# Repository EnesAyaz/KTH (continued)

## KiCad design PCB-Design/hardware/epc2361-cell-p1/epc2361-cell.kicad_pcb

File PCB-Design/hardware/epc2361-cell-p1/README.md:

# P1: EPC-style one-pair power-loop layout

This is the revised native KiCad 7 project requested from EPC's optimal-loop illustration. The original P0 project is preserved in the sibling directory. Open `epc2361-cell.kicad_pro` here.

## What changed

- 27 x 30 mm study outline. One high-side EPC2361 at (15,16) mm and one low-side at (15,22) mm; 6 mm pitch.
- Six 0805 capacitors across the top above the high-side device, with positive terminals facing the devices. Broad top DC+ copper replaces the long side rail.
- Capacitor negative terminals connect through paired vias to the first inner DC- layer. Low-side source vias complete the return directly beneath the top power path.
- Six optional/DNP bottom capacitors sit underneath the top bank. Their rail transitions are outside the device lands. The DC+ via antipads perforate L2 locally but leave a continuous return; their effect needs extraction. Bottom parts are not assumed equally effective at high frequencies.
- No driver IC. Individual top G/Kelvin-source contact pairs, series gate-resistor sites and optional local gate-source resistors remain.
- All power ports and seven probe pads are routed. Pads are interface placeholders, not selected or rated power sockets. Probe mapping: TP1 GH, TP2 high-side source/AC, TP3 GL, TP4 low-side source/DC-, TP5 DC+, TP6 DC-, TP7 AC.
- Insulated top cold-plate contact corridor reserved over the FET pair. Full plate, TIM, mounting and clamping remain mechanical design work.

## Capacitors

C1-C6: TDK C2012X7S2A105K125AB, 1 uF / 100 V / X7S / 0805, six populated provisionally. C7-C12 use the same part but are DNP until impedance and heating justify population. Nominal capacitance is 6 uF top-only or 12 uF with both banks; neither number is the retained capacitance at 75 V.

TDK's simple equivalent-circuit model gives 0.480 nH for this component. The six-capacitor ideal uncoupled component-only result is 0.080 nH. This excludes mounting, shared copper, vias, FET interconnections and coupling, and is not the complete loop inductance. The 1210 alternative has 0.600 nH model inductance and more nominal capacitance. These are conventional MLCCs selected for a low-inductance assembled bank; no suitable 100 V reverse-geometry part was verified.

See `../../docs/capacitor-selection-p1.md` for manufacturer links, alternatives and qualification limits. C at 75 V and capacitor RMS heating remain unqualified. External bulk capacitance is still required.

## Proposed stackup

The board file records a provisional four-layer stack: 70 um top copper, 100 um prepreg to the 35 um L2 return, 1.19 mm core, 35 um L3, 100 um prepreg, and 70 um bottom copper. Copper plus dielectric totals 1.60 mm before solder mask. FR4 electrical properties are placeholders, not a selected laminate. Fabricator confirmation is required. L3 currently has no functional plane; layer count alone does not reduce the loop.

The key optimization parameter is the 0.10 mm top-to-L2 separation. A parallel-plate estimate must use the actual overlapping current corridor and include transitions separately. No extracted or measured inductance is claimed.

## Checks and release status

30 components and 60 pin assignments match the KiCad-exported schematic netlist and PCB. Native PCB DRC: zero violations, zero unconnected pads, zero footprint errors. Native schematic ERC has not been run. Views: `top.svg`, `return.svg`, `bottom.svg`; PNG previews alongside them. Bottom export is viewed through the board from above unless mirrored in KiCad.

This is a routed engineering study, not a manufacturing release or a demonstrated 36.7 A RMS cell rating. Wide power distribution, terminal ratings, assembly footprint sign-off, capacitor derating, coupled parasitic extraction, switching tests and electrothermal validation are outstanding. The six-parallel module and gate-driver PCB are deferred.

## Rebuild

Run `scripts/build_cell_p1.py` with KiCad Python. Set `CELL_REVISION=epc2361-cell-p1`, run `scripts/build_cell_schematic.py`, export the XML netlist to this folder, then run `scripts/check_cell.py` with the same environment variable. The audit fills zones and writes the DRC report. Preserve manual edits before regenerating.

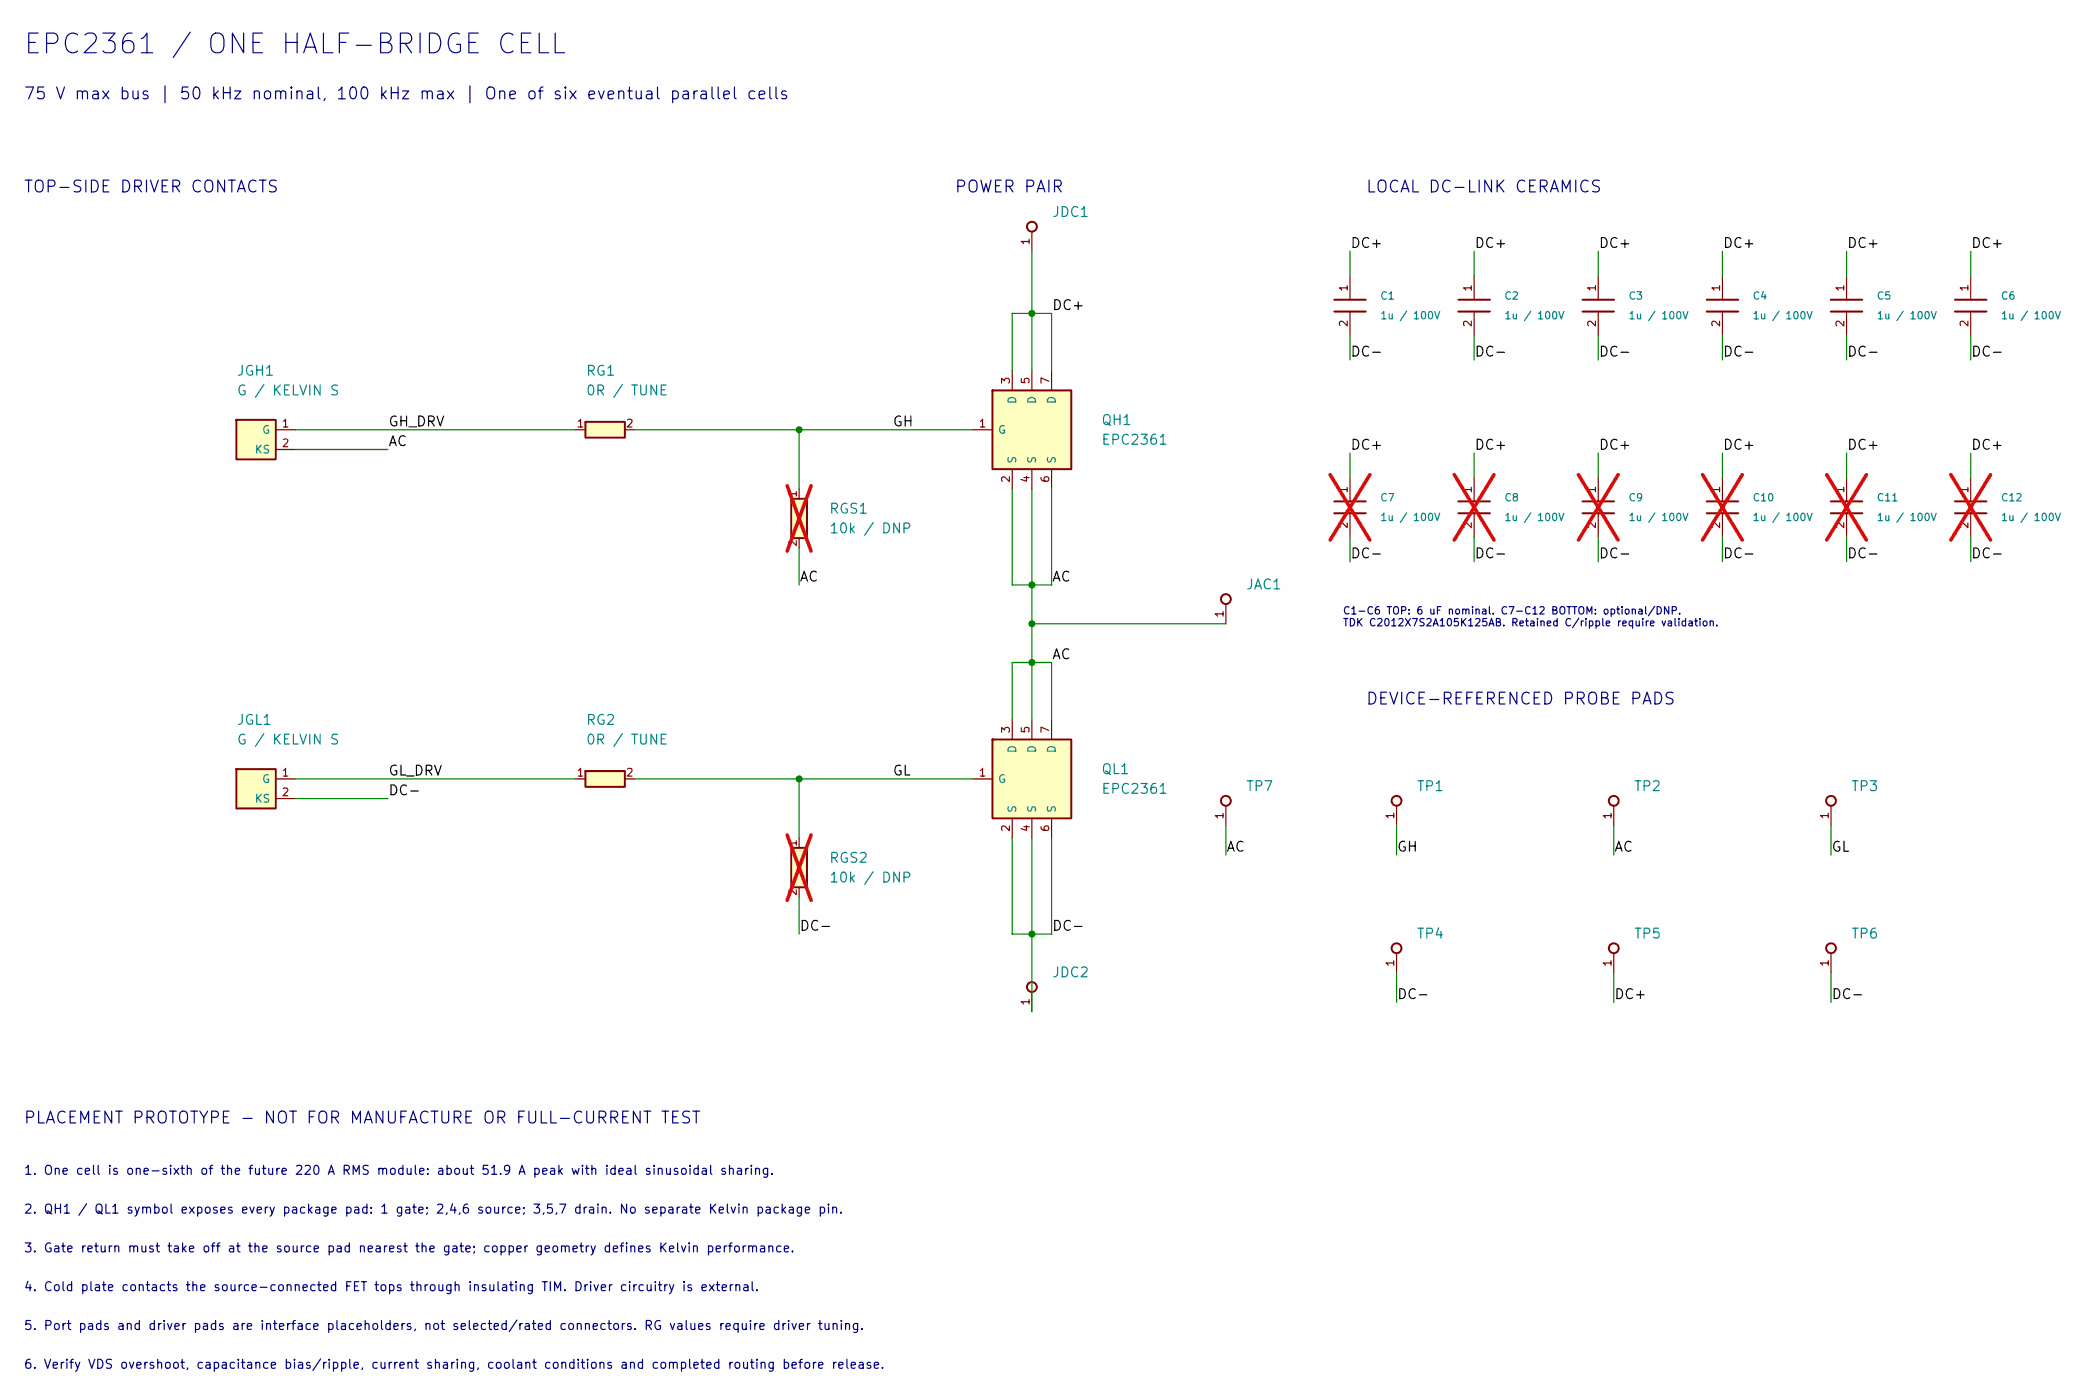
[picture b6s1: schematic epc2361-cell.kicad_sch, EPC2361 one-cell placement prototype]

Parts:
C1, C2, C3, C4, C5, C6: 1u / 100V; C_0805_2012Metric
C7, C8, C9, C10, C11, C12: 1u / 100V; C_0805_2012Metric; not fitted
JAC1: AC PORT PAD; Power_Port_Pad
JDC1: DC+ PORT PAD; Power_Port_Pad
JDC2: DC- PORT PAD; Power_Port_Pad
JGH1: G / KELVIN S; Gate_Source_Pads
JGL1: G / KELVIN S; Gate_Source_Pads
QH1: EPC2361
QL1: EPC2361
RG1, RG2: 0R / TUNE; R_0402_1005Metric
RGS1, RGS2: 10k / DNP; R_0402_1005Metric; not fitted
TP1: GH; Probe_Pad
TP2, TP7: AC; Probe_Pad
TP3: GL; Probe_Pad
TP4, TP6: DC-; Probe_Pad
TP5: DC+; Probe_Pad

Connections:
AC: JAC1.1, JGH1.2 (KS), QH1.2 (S), QH1.4 (S), QH1.6 (S), QL1.3 (D), QL1.5 (D), QL1.7 (D), RGS1.2, TP2.1, TP7.1
DC+: C1.1, C2.1, C3.1, C4.1, C5.1, C6.1, C7.1, C8.1, C9.1, C10.1, C11.1, C12.1, JDC1.1, QH1.3 (D), QH1.5 (D), QH1.7 (D), TP5.1
DC-: C1.2, C2.2, C3.2, C4.2, C5.2, C6.2, C7.2, C8.2, C9.2, C10.2, C11.2, C12.2, JDC2.1, JGL1.2 (KS), QL1.2 (S), QL1.4 (S), QL1.6 (S), RGS2.2, TP4.1, TP6.1
GH: QH1.1 (G), RG1.2, RGS1.1, TP1.1
GH_DRV: JGH1.1 (G), RG1.1
GL: QL1.1 (G), RG2.2, RGS2.1, TP3.1
GL_DRV: JGL1.1 (G), RG2.1

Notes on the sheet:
EPC2361 / ONE HALF-BRIDGE CELL
75 V max bus | 50 kHz nominal, 100 kHz max | One of six eventual parallel cells
TOP-SIDE DRIVER CONTACTS
POWER PAIR
LOCAL DC-LINK CERAMICS
C1-C6 TOP: 6 uF nominal. C7-C12 BOTTOM: optional/DNP. TDK C2012X7S2A105K125AB. Retained C/ripple require validation.
DEVICE-REFERENCED PROBE PADS
PLACEMENT PROTOTYPE - NOT FOR MANUFACTURE OR FULL-CURRENT TEST
1. One cell is one-sixth of the future 220 A RMS module: about 51.9 A peak with ideal sinusoidal sharing.
2. QH1 / QL1 symbol exposes every package pad: 1 gate; 2,4,6 source; 3,5,7 drain. No separate Kelvin package pin.
3. Gate return must take off at the source pad nearest the gate; copper geometry defines Kelvin performance.
4. Cold plate contacts the source-connected FET tops through insulating TIM. Driver circuitry is external.
5. Port pads and driver pads are interface placeholders, not selected/rated connectors. RG values require driver tuning.
6. Verify VDS overshoot, capacitance bias/ripple, current sharing, coolant conditions and completed routing before release.

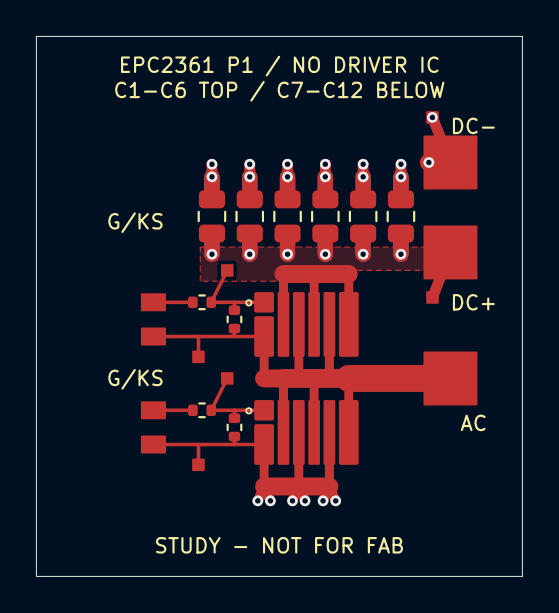
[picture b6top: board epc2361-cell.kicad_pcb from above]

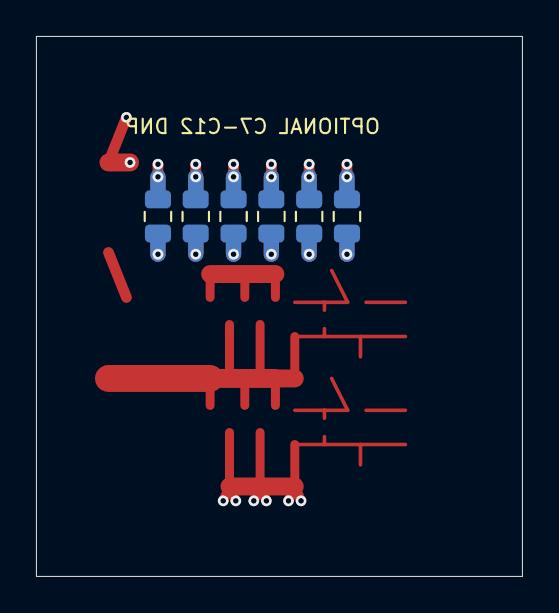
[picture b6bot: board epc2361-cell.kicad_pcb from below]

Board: 4 copper layers, 27.0 x 30.0 mm, 30 parts (6 on the bottom side), 7 nets.

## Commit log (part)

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2023-03-22 I will update this repo weekly with a report.
2023-04-24 I create a iterative loss analysis for only conduction losses
2023-04-24 switching loss is added
2023-04-25 established structs and generalized the script
2023-05-17 a new start
2023-05-30 weekly reports
    small literature review for bearing current is made
2023-05-31 updating the presentations
2023-06-02 weekly report about mitigation of bearing current
2023-06-05 Weekly reports are combined in Stepwise Design
2023-06-05 online carrier phase shift calculation to reduce the CMV
2023-06-05 for loop is created to calculate the phase requirements
2023-06-06 phases are calculated, it is a "paper" idea !!!
2023-06-06 updated version
2023-06-07 the presentation and analytic switching loop are updated
2023-06-07 presentation update
2023-06-08 create comparative analysis
2023-06-12 comparative analysis are added
2023-06-13 comparative analysis
2023-06-15 conduction losses and switching losses
2023-06-18 Hemizero presentation
2023-07-04 new common mode reduction method
    matlab model is created, a presentation is created
2023-07-04 loss calculations, for 2L and 3L converters
2023-07-18 dv/dt
2023-07-18 updated presentation
2023-08-29 weekly reports
2023-09-14 inmotion presentation
2023-09-14 inductance desing
2023-09-14 savings
2023-09-18 adding presentations
2023-10-04 gitignore
2023-11-16 loss calculation
2023-11-16 inductance
2023-11-16 modulation
2024-04-21 Drive cycle analysis
2024-04-21 loss calculation models
2024-04-21 ECCE paper draft and first submission
2024-04-21 weekly reports updates
2024-04-21 update 2
2024-04-21 Imperix
2024-08-07 capacitor sizing
2024-08-07 ecce
2024-08-07 harmonic loss modelling
2024-08-07 simulink models
2024-08-07 loss calculations
2024-08-07 common mode voltage model
2024-08-07 presentations and specs
2024-08-21 simulink three phase
2024-09-06 weekly reports update
2024-10-01 access paper documents, first files
2024-10-25 presentation of the meeting updates
2024-10-25 specs copyright
2024-10-25 access paper about CMV
2024-11-06 articles
2024-11-06 airgap harmonics
2024-11-06 IEMDC paper
    IEMDC paper- 2level calculations are written. In my SPEC paper, I found miscalculation in rds_on. We should come back to it later.
2024-11-07 weekly reports
    weekly reports about PWM generation and current waveforms with switching ripple
2024-11-11 Airgap harmonics and some technical documents
    airgap harmonics, first proposal are done. TI initialization and PCB documents are added.
2024-11-15 Update .gitignore
    ansys results file are ignored
2024-11-15 Update airgap harmonics.pptx
    airgap harmonic utilization- first idea
2024-11-15 Ansys models for DC-link impedance model
2024-11-15 .cir files from ansys
    netlist of impedance matrix, including resistances and inductances
2024-11-15 Ltspice model for Dc link modelling
2024-11-15 matlab files for DC-link modelling
    We should think about the resonant structure, and should we try operating a frequency give the uneven current distribution
2024-11-26 Ltspice files for DC bus and gitignore
2024-11-26 data, parasitic circuits for 3 phase
2024-11-26 matlab to get the response for SPWM of 3 phase
2024-11-26 ansys model and reports etc
2024-11-26 weekly report for harmonic modelling
2024-12-18 weekly reports on harmonic model of the inverter
2025-01-03 draft version of BOM for the first prototype
2025-02-14 ECCE-2024 update
2025-02-14 ECCE-2025 first files and IEMDC the codes for final submission
2025-02-23 ECCE 2025 and Access Paper
2025-02-24 ECCE-2025 Experimental figures
2025-02-26 2Level code for current waveforms and gitignore for mat, raw and log files
2025-02-26 three level simulations
2025-02-26 gitignore zip files
2025-02-28 Back2back inverter with Wolfspeed Model, gate drivers
2025-03-05 IEMDC-2025 waveforms updated and checked FFT
2025-03-05 Updating BOM of first prototype
2025-03-05 B2B inverter and three phase inverter LTSpice model
2025-03-10 presentation about scania visit
2025-03-10 Ttype modulation
2025-03-11 2 level and 3 level losses for IEMDC
2025-03-19 back2back inverter simulink model
    Ttype modulation SVPWM
2025-03-24 back-to-back
2025-03-25 hemizero meeting
2025-04-04 B2B inductor design
2025-04-04 Prototyping BOM and presentations
2025-04-04 git ignore
2025-04-04 ACCESS paper, simulations and imperix code. Inductance and capacitance values will be selected.
2025-04-22 gitignores and presentations
2025-04-22 experimental figures osciloscope for CMV journal paper
2025-04-22 experimental raw data codes for CMV journal
2025-04-22 imperix codes
2025-04-22 raw data- CMV journal
2025-04-22 ignore the raw data
2025-04-23 experimental figures were updated, and finalized the paper and cover letter
2025-04-23 update gitignore for raw data
2025-05-19 Capacitor DC-link current minimization
2025-05-19 ECCE-2025- simulations
2025-05-19 Prototyping
2025-05-20 ECCE2025 and bearing current model
2025-07-10 ECCE-2025
2025-07-10 Bearing current and misc
2025-07-18 capacitor-sizing journal, drawings for intro and modulation
2025-07-18 prototyping single phase inverter
2025-07-29 capacitor sizing ripple minimization
2025-08-12 capacitor sizing- LUT
2025-10-08 field excitation, transition gift
2025-10-08 harmonic loss modeling paper started
2025-10-08 protoyping control three phase is created
2025-10-08 CMV paper FFT results
2025-10-14 multiphaseproductsEV and CMV paper simulink
2025-10-30 1.2kV access paper codes and several updates
2025-11-07 1.2kV journal paper files
2025-12-15 1.2kV Paper Graphs
2025-12-15 Update gitignore
2025-12-15 Staff Meeting and 50 Percent meeting
2025-12-15 Colorimetric Setup
2026-01-23 new drawings for 1.2kV Paper
2026-02-09 Auxliary power supply elimination
2026-03-30 auxliary power module elimination
2026-04-29 1.2kV submission
2026-04-29 OPT field excitation
2026-04-29 miscellaneous
2026-05-18 mitigation of CMV - OJPEL files
2026-05-18 IPEC 2026 Poster
2026-05-18 loss calculations harmonics
